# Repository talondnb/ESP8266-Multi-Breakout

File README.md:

# ESP8266-Multi-Breakout

This is an ESP8266 [NodeMCU V3 LoLin](https://www.aliexpress.com/item/ESP8266-CH340G-CH340-G-NodeMcu-V3-Lua-Wireless-WIFI-Module-Connector-Development-Board-Based-ESP-12E/32800966224.html) break-out PCB I've created for use with Home Assistant. I created this layout to allow for various functions; a garage door opener or retrofitting to a 'dumb' alarm system to integrate existing PIRs into your smart home setup.

The board will accept a +12VDC, 1A input via a 2.1MM centre positive jack. This voltage is regulated down to +5VDC via the onboard [AMS1117-5.0 linear regulator](http://www.advanced-monolithic.com/pdf/ds1117.pdf) to feed power to the two +5V relays and the NodeMCU V3.

The board also accommodates the following sensors:

[**DHT22**](https://www.aliexpress.com/item/DHT22-single-bus-digital-temperature-and-humidity-sensor-module-2302-electronic-building-blocks/32753887461.html) - Temperature and Humidity sensor

[**HC-SR04**](https://www.aliexpress.com/item/1pcs-HC-SR04-to-world-Ultrasonic-Wave-Detector-Ranging-Module-for-arduino-Distance-Sensor/32786781050.html) - Ultrasonic distance sensor

Aside from the above, a [LM339N](http://www.ti.com/lit/ds/symlink/lm339.pdf) is also available onboard and powered by the +12VDC input. This can be used to integrate your existing alarm system, to make use of the PIRs as binary sensors for motion detection without affecting the functionality of the original system. See [here](https://www.instructables.com/id/Alarm-PIR-Movement-to-Home-Automation/) for more information.

Pin out as follows:

| Pin  | Function | Comment
| ------------- | ------------- | ------------- |
| D0  | N/A  | Not used |
| D1  | Z1 or DHT22 input  | Only single input allowed |
| D2  | Z2 or other input  | Input/output |
| D3  | Z3 or other input  | Input/output |
| D4  | Z4 or other input  | Input/output |
| D5  | HC-SR04 (Trig)  | Ultrasonic distance sensor (if used) |
| D6  | HC-SR04 (Echo)  | Ultrasonic distance sensor (if used) |
| D7  | Relay #1  | Relay #1 trigger |
| D8  | Relay #2  | Relay #2 trigger |

See here for [pin reference](https://github.com/thehookup/Wireless_MQTT_Doorbell/blob/master/GPIO_Limitations_ESP8266_NodeMCU.jpg). 

Integration to Home Assistant can be done using the [esphomeyaml library](https://esphomelib.com/esphomeyaml/index.html).

This design was created using Eagle 7.3.

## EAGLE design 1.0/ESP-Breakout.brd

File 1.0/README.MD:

D0	Free
D1	DHT22 (Temperature/Humidity)	
D2	Free
D3	Free
D4	Free
D5	HC-SR04 (Trig)
D6	HC-SR04 (Echo)
D7	Relay 1
D8	Relay 2

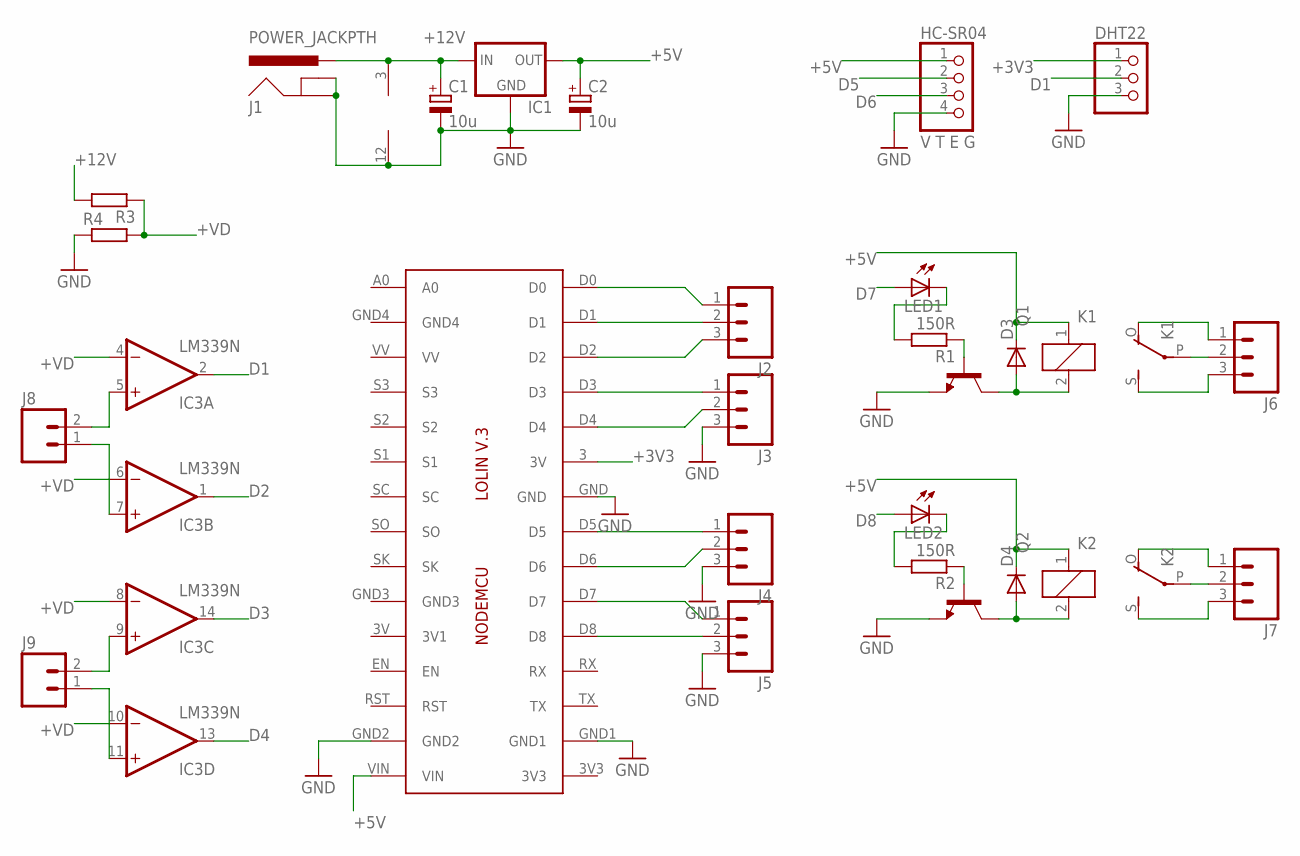
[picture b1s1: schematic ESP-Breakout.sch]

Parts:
C1, C2: 10u; A/3216-18W
D3, D4: DIODE-DO214AC; DO214AC
DHT22: PINHD-1X3/90; 1X03/90
HC-SR04: V T E G; 1X04
IC1: LM1117; SOT223
IC2: LOLINV3
IC3: LM339N; DIL14
J1: POWER_JACKPTH; POWER_JACK_PTH
J2, J3, J4, J5, J6, J7: M03-SCREW-5MM; SCREWTERMINAL-5MM-3
J8, J9: M025MM; SCREWTERMINAL-5MM-2
K1, K2: ZF112
LED1, LED2: LEDCHIP-LED0805; CHIP-LED0805
Q1, Q2: BC850SMD; SOT23-BEC
R1, R2: 150R; R0805
R3, R4: R-EU_0204/7; 0204/7

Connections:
+3V3: DHT22.1, IC2.3 (3V)
+5V: C2.+, D3.C, D4.C, HC-SR04.1, IC1.2 (OUT), IC2.VIN, K1.1, K2.1
+12V: C1.+, IC1.3 (IN), IC3.3 (V+), J1.PWR, R3.2
+VD: IC3.4 (-IN), IC3.6 (-IN), IC3.8 (-IN), IC3.10 (-IN), R3.1, R4.2
D0: IC2.D0, J2.1
D1: DHT22.2, IC2.D1, IC3.2 (OUT), J2.2
D2: IC2.D2, IC3.1 (OUT), J2.3
D3: IC2.D3, IC3.14 (OUT), J3.1
D4: IC2.D4, IC3.13 (OUT), J3.2
D5: HC-SR04.2, IC2.D5, J4.1
D6: HC-SR04.3, IC2.D6, J4.2
D7: IC2.D7, J5.1, LED1.A
D8: IC2.D8, J5.2, LED2.A
GND: C1.-, C2.-, DHT22.3, HC-SR04.4, IC1.1 (GND), IC2.GND, IC2.GND1, IC2.GND2, IC3.12 (GND), J1.GND, J1.GNDBREAK, J3.3, J4.3, J5.3, Q1.E, Q2.E, R4.1
unnamed: IC3.5 (+IN), J8.2
unnamed: IC3.7 (+IN), J8.1
unnamed: IC3.9 (+IN), J9.2
unnamed: IC3.11 (+IN), J9.1
unnamed: J6.2, K1.P
unnamed: J6.3, K1.S
unnamed: J6.1, K1.O
unnamed: J7.2, K2.P
unnamed: J7.1, K2.O
unnamed: J7.3, K2.S
unnamed: D3.A, K1.2, Q1.C
unnamed: D4.A, K2.2, Q2.C
unnamed: Q1.B, R1.1
unnamed: Q2.B, R2.1
unnamed: LED1.C, R1.2
unnamed: LED2.C, R2.2

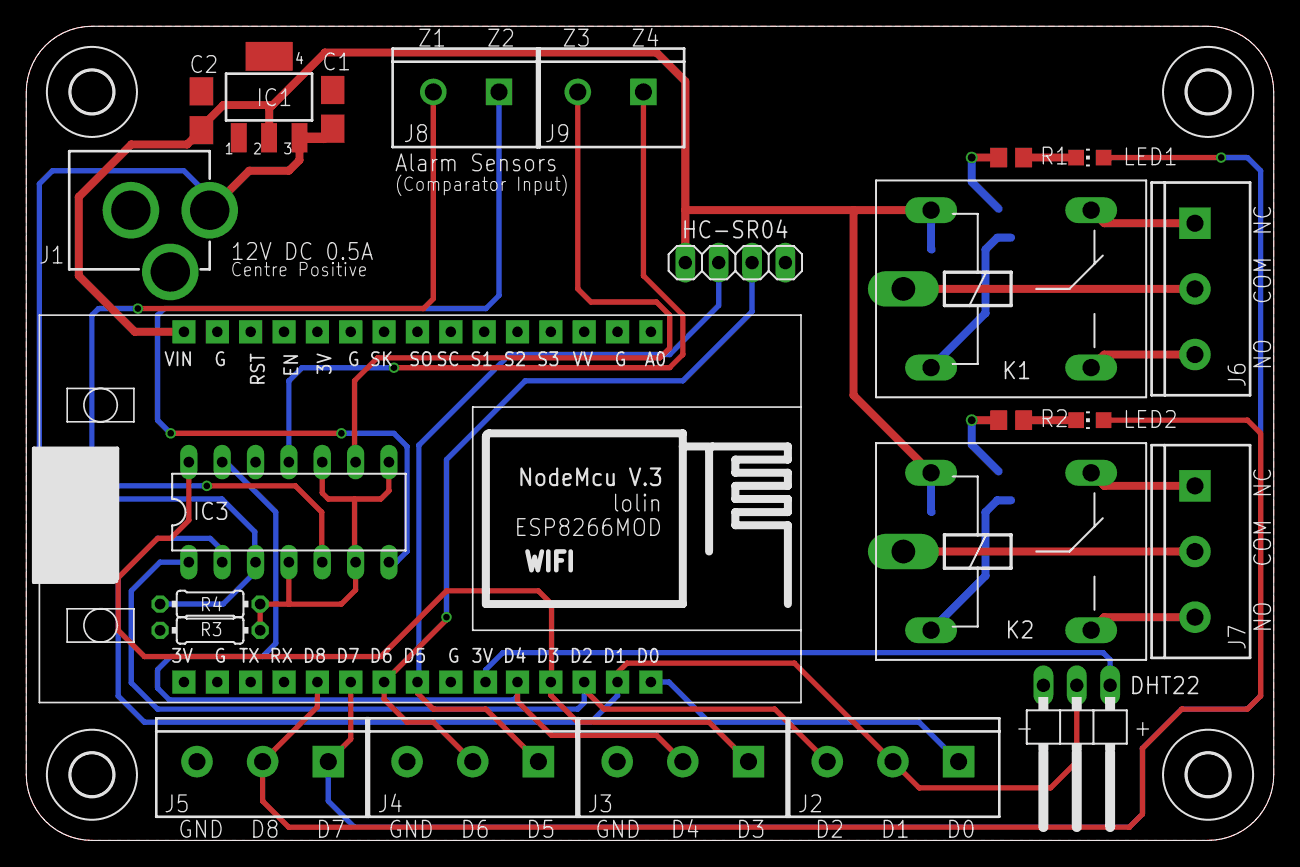
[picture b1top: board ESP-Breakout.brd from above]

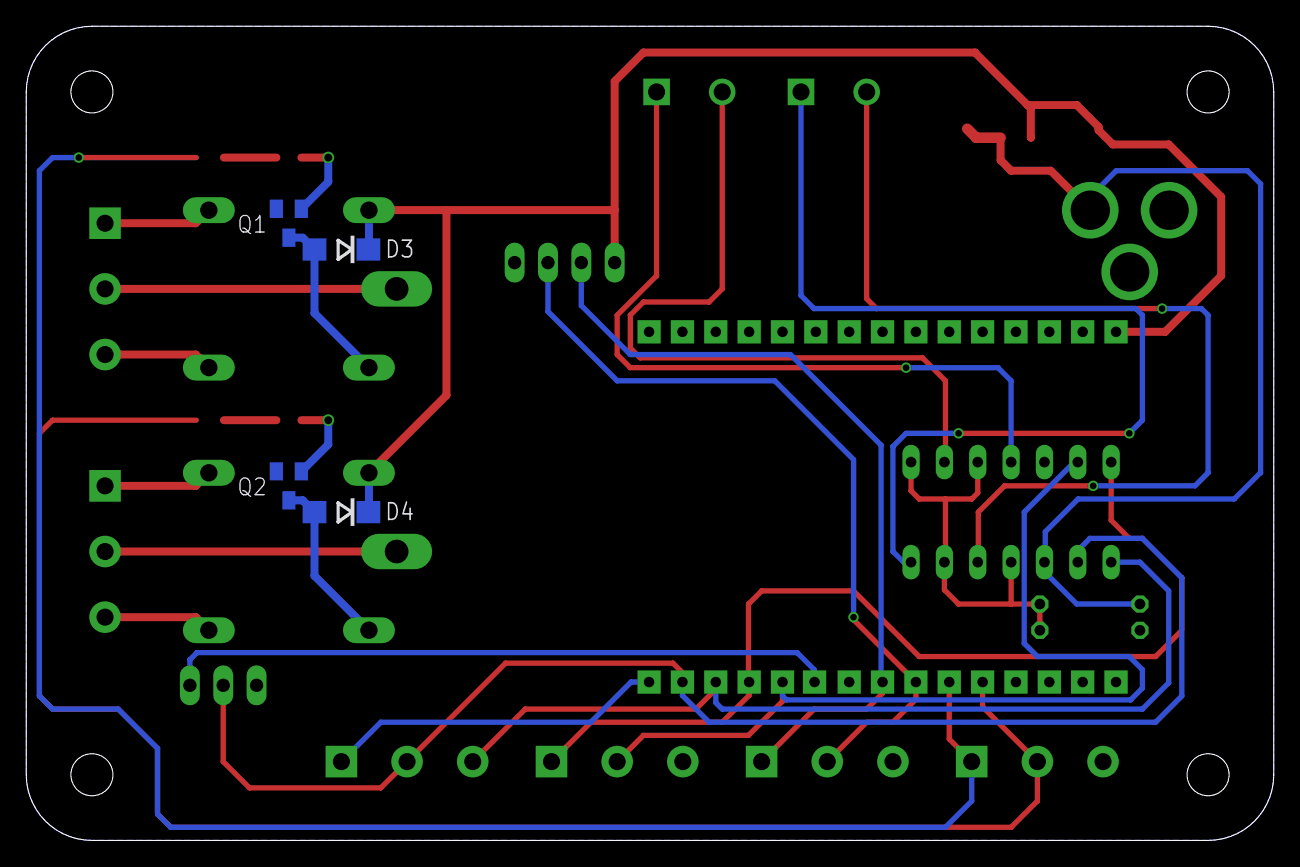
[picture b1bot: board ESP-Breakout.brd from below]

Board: 2 copper layers, 95.0 x 62.0 mm, 32 parts (4 on the bottom side), 30 nets.

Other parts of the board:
U$2, U$3, U$4, U$5: 3,2

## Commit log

2019-01-05 This is an ESP8266 (NodeMCU V3 LoLin) break-out PCB I've created for use with Home Assistant.
    This is an ESP8266 (NodeMCU V3 LoLin) break-out PCB I've created for use with Home Assistant.
2019-01-05 Added image

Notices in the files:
parts and their libraries:
SparkFun-Connectors: Licensing: Creative Commons ShareAlike 4.0 International - https://creativecommons.org/licenses/by-sa/4.0
